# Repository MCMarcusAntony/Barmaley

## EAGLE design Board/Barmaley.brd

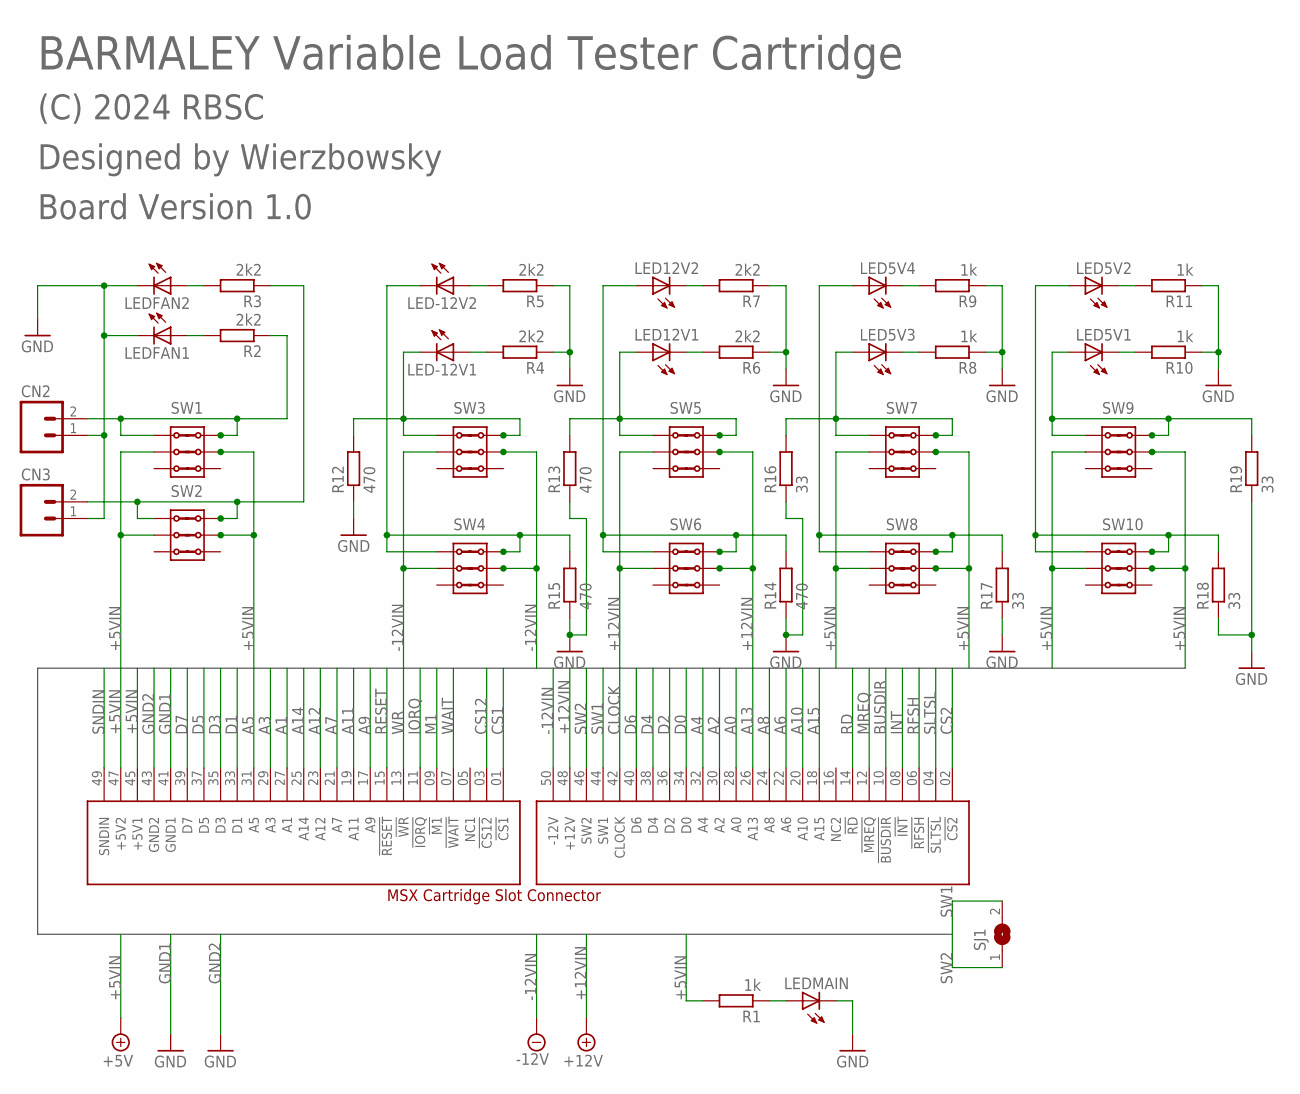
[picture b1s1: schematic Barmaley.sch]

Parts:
CN1: SLOTCONN; MSX_SLOT_CON
CN2, CN3: 2-PIN_FAN_CONNECTOR; MOLEX-X2
LED5V1, LED5V2, LED5V3, LED5V4, LED12V1, LED12V2: LEDSQR2X5; LED2X5
LED-12V1, LED-12V2: LEDSQR2X5; LED2X5
LEDFAN1, LEDFAN2: LEDSQR2X5; LED2X5
LEDMAIN: LED5MM
R1, R8, R9, R10, R11: 1k; R0805
R2, R3, R4, R5, R6, R7: 2k2; R0805
R12, R13, R14, R15: 470; 0617/22
R16, R17, R18, R19: 33; 0617/22
SJ1: SJ
SW1, SW2, SW3, SW4, SW5, SW6, SW7, SW8, SW9, SW10: 2-POSITION_SWITCH; 2PSW

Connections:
+5VIN: CN1.45 (+5V1), CN1.47 (+5V2), R1.2, SW1.2.1, SW1.2.2, SW2.2.1, SW2.2.2, SW7.2.1, SW7.2.2, SW8.2.1, SW8.2.2, SW9.2.1, SW9.2.2, SW10.2.1, SW10.2.2
+12VIN: CN1.48 (+12V), SW5.2.1, SW5.2.2, SW6.2.1, SW6.2.2
-12VIN: CN1.50 (-12V), SW3.2.1, SW3.2.2, SW4.2.1, SW4.2.2
A0: CN1.28 (A0)
A1: CN1.27 (A1)
A2: CN1.30 (A2)
A3: CN1.29 (A3)
A4: CN1.32 (A4)
A5: CN1.31 (A5)
A6: CN1.22 (A6)
A7: CN1.21 (A7)
A8: CN1.24 (A8)
A9: CN1.17 (A9)
A10: CN1.20 (A10)
A11: CN1.19 (A11)
A12: CN1.23 (A12)
A13: CN1.26 (A13)
A14: CN1.25 (A14)
A15: CN1.18 (A15)
BUSDIR: CN1.10 (!BUSDIR)
CLOCK: CN1.42 (CLOCK)
CS1: CN1.01 (!CS1)
CS2: CN1.02 (!CS2)
CS12: CN1.03 (!CS12)
D0: CN1.34 (D0)
D1: CN1.33 (D1)
D2: CN1.36 (D2)
D3: CN1.35 (D3)
D4: CN1.38 (D4)
D5: CN1.37 (D5)
D6: CN1.40 (D6)
D7: CN1.39 (D7)
GND: CN2.1, CN3.1, LEDFAN1.K (C), LEDFAN2.K (C), LEDMAIN.K (C), R4.1, R5.1, R6.1, R7.1, R8.1, R9.1, R10.1, R11.1, R12.1, R13.1, R14.1, R15.1, R16.1, R17.1, R18.1, R19.1
GND1: CN1.41 (GND1)
GND2: CN1.43 (GND2)
GND3: LED-12V1.K (C), R12.2, SW3.3.1, SW3.3.2
GND4: LED-12V2.K (C), R15.2, SW4.3.1, SW4.3.2
INT: CN1.08 (!INT)
IORQ: CN1.11 (!IORQ)
M1: CN1.09 (!M1)
MREQ: CN1.12 (!MREQ)
unnamed: LEDMAIN.A, R1.1
unnamed: CN2.2, R2.1, SW1.3.1, SW1.3.2
unnamed: CN3.2, R3.1, SW2.3.1, SW2.3.2
unnamed: LEDFAN1.A, R2.2
unnamed: LEDFAN2.A, R3.2
unnamed: LED-12V1.A, R4.2
unnamed: LED-12V2.A, R5.2
unnamed: LED12V1.K (C), R6.2
unnamed: LED12V2.K (C), R7.2
unnamed: LED5V4.K (C), R9.2
unnamed: LED5V3.K (C), R8.2
unnamed: LED5V1.K (C), R10.2
unnamed: LED5V2.K (C), R11.2
unnamed: LED12V1.A, R13.2, SW5.3.1, SW5.3.2
unnamed: LED12V2.A, R14.2, SW6.3.1, SW6.3.2
unnamed: LED5V4.A, R17.2, SW8.3.1, SW8.3.2
unnamed: LED5V3.A, R16.2, SW7.3.1, SW7.3.2
unnamed: LED5V1.A, R19.2, SW9.3.1, SW9.3.2
unnamed: LED5V2.A, R18.2, SW10.3.1, SW10.3.2
RD: CN1.14 (!RD)
RESET: CN1.15 (!RESET)
RFSH: CN1.06 (!RFSH)
SLTSL: CN1.04 (!SLTSL)
SNDIN: CN1.49 (SNDIN)
SW1: CN1.44 (SW1), SJ1.2
SW2: CN1.46 (SW2), SJ1.1
WAIT: CN1.07 (!WAIT)
WR: CN1.13 (!WR)

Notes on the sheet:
BARMALEY Variable Load Tester Cartridge
(C) 2024 RBSC
Designed by Wierzbowsky
Board Version 1.0

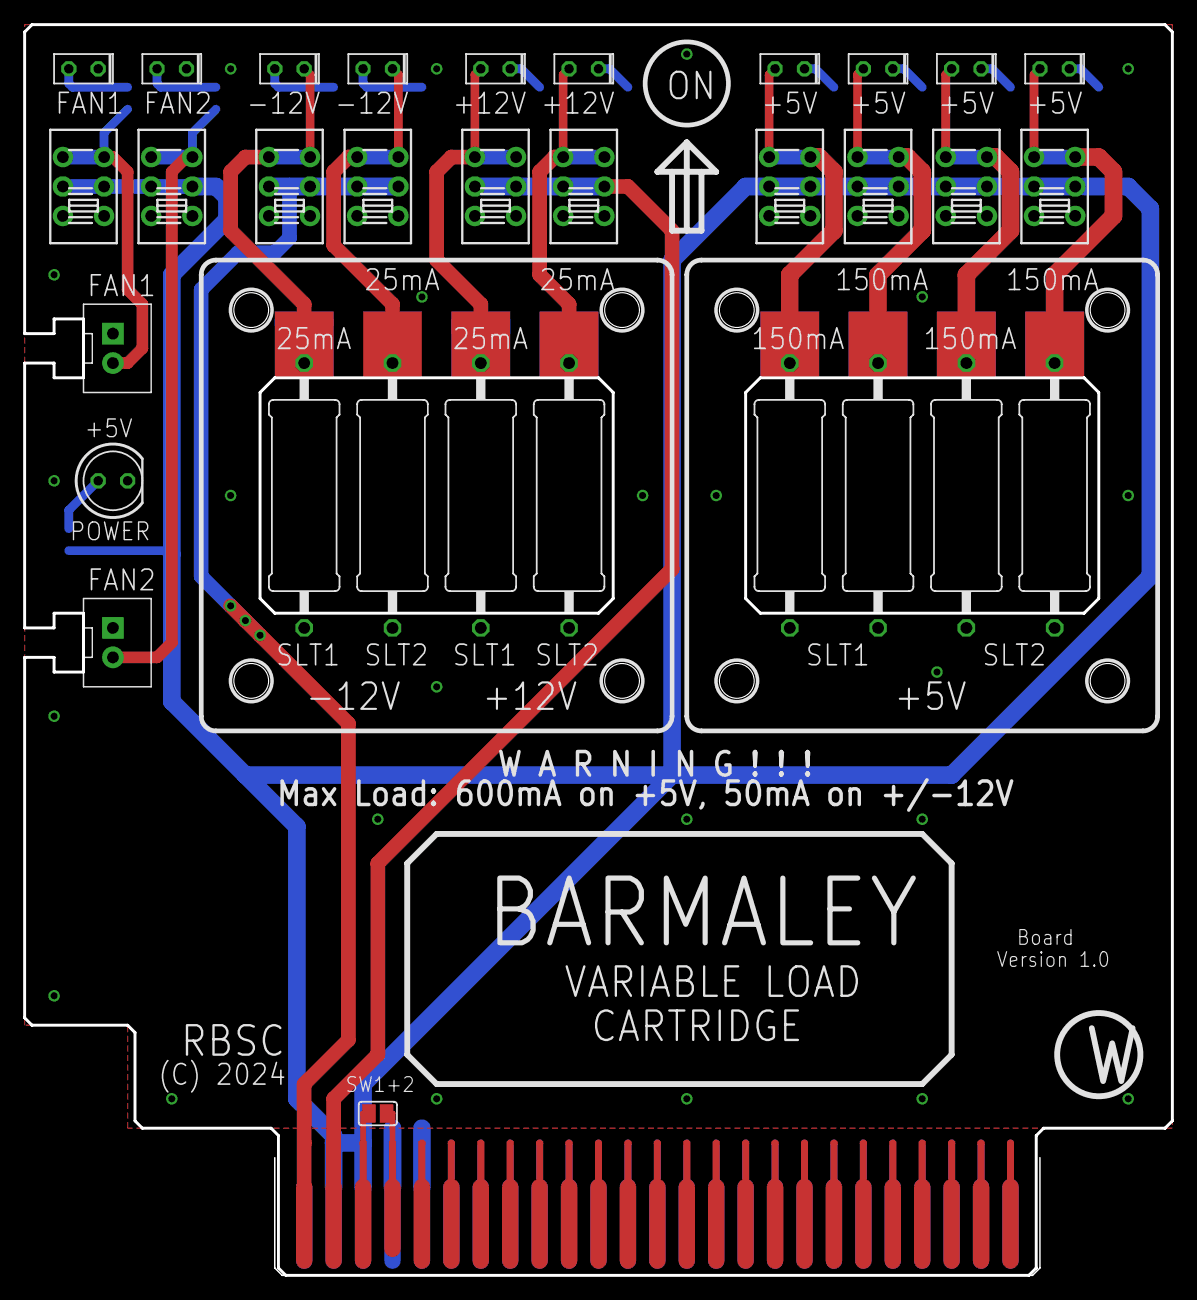
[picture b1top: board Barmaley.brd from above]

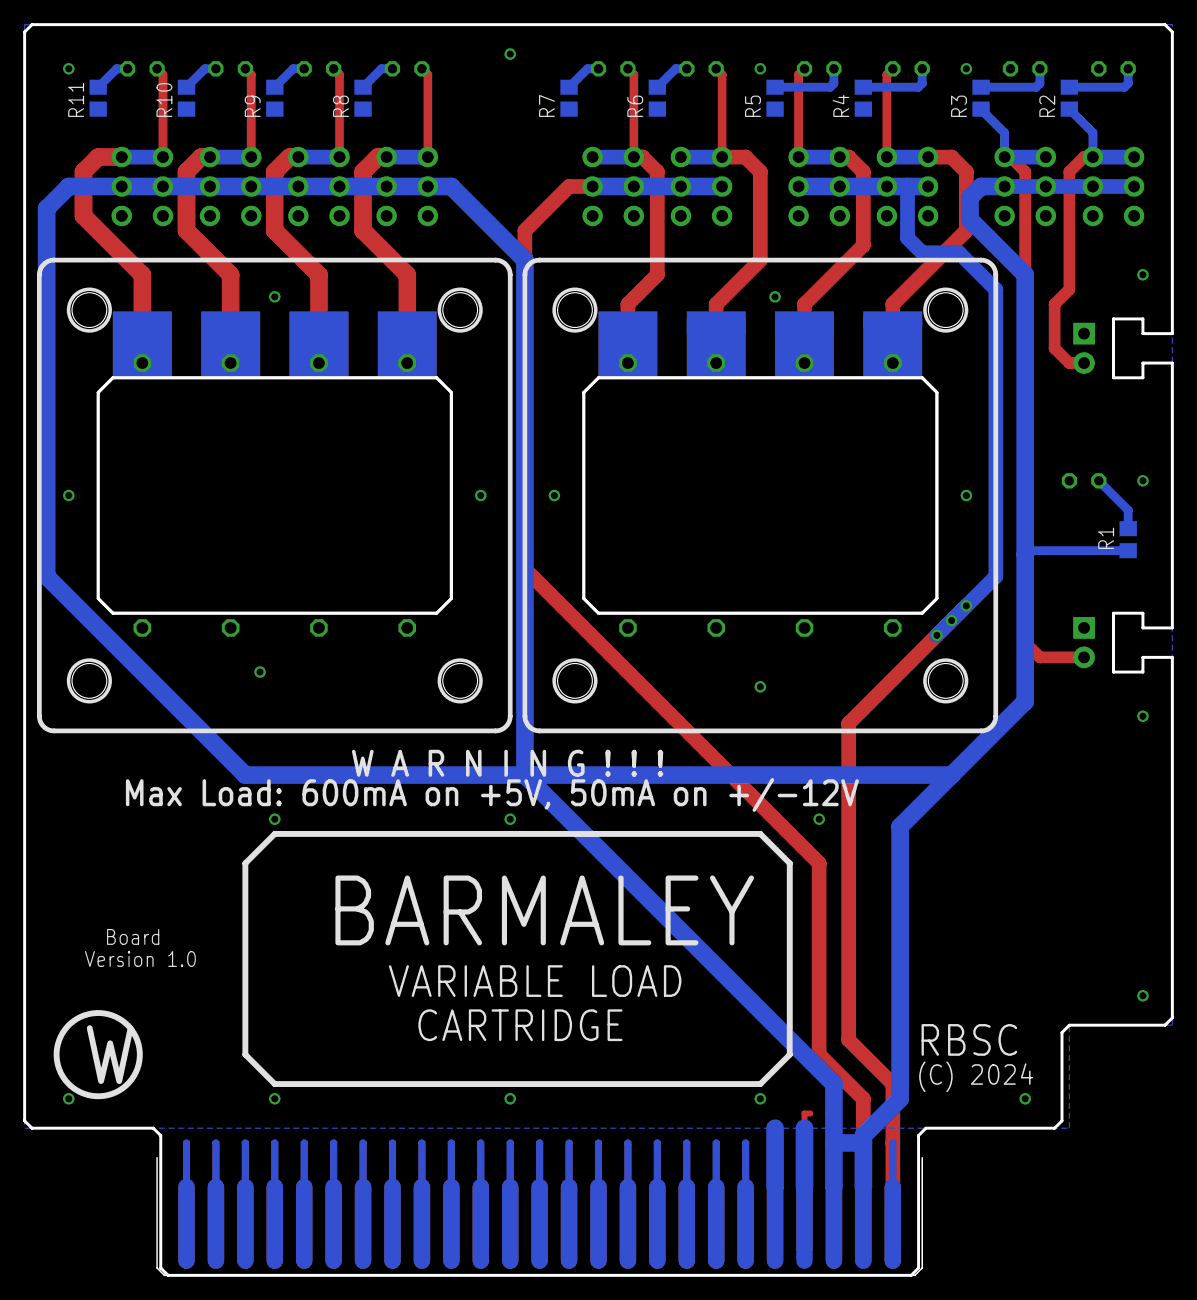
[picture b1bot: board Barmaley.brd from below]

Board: 2 copper layers, 99.1 x 108.0 mm, 44 parts (11 on the bottom side), 27 nets.

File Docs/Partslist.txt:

Partlist

Assembly variant: 

Part     Value               Device              Package      Library       Sheet

CN2      2-PIN_FAN_CONNECTOR 2-PIN_FAN_CONNECTOR MOLEX-X2     fan_conn      1
CN3      2-PIN_FAN_CONNECTOR 2-PIN_FAN_CONNECTOR MOLEX-X2     fan_conn      1
LED-12V1                     LEDSQR2X5           LED2X5       led           1
LED-12V2                     LEDSQR2X5           LED2X5       led           1
LED5V1                       LEDSQR2X5           LED2X5       led           1
LED5V2                       LEDSQR2X5           LED2X5       led           1
LED5V3                       LEDSQR2X5           LED2X5       led           1
LED5V4                       LEDSQR2X5           LED2X5       led           1
LED12V1                      LEDSQR2X5           LED2X5       led           1
LED12V2                      LEDSQR2X5           LED2X5       led           1
LEDFAN1                      LEDSQR2X5           LED2X5       led           1
LEDFAN2                      LEDSQR2X5           LED2X5       led           1
LEDMAIN                      LED5MM              LED5MM       led           1
R1       1k                  R-EU_R0805          R0805        resistor      1
R2       2k2                 R-EU_R0805          R0805        resistor      1
R3       2k2                 R-EU_R0805          R0805        resistor      1
R4       2k2                 R-EU_R0805          R0805        resistor      1
R5       2k2                 R-EU_R0805          R0805        resistor      1
R6       2k2                 R-EU_R0805          R0805        resistor      1
R7       2k2                 R-EU_R0805          R0805        resistor      1
R8       1k                  R-EU_R0805          R0805        resistor      1
R9       1k                  R-EU_R0805          R0805        resistor      1
R10      1k                  R-EU_R0805          R0805        resistor      1
R11      1k                  R-EU_R0805          R0805        resistor      1
R12      470                 R-EU_0617/22        0617/22      resistor      1
R13      470                 R-EU_0617/22        0617/22      resistor      1
R14      470                 R-EU_0617/22        0617/22      resistor      1
R15      470                 R-EU_0617/22        0617/22      resistor      1
R16      33                  R-EU_0617/22        0617/22      resistor      1
R17      33                  R-EU_0617/22        0617/22      resistor      1
R18      33                  R-EU_0617/22        0617/22      resistor      1
R19      33                  R-EU_0617/22        0617/22      resistor      1
SW1      2-POSITION_SWITCH   2-POSITION_SWITCH   2PSW         2pos_switch   1
SW2      2-POSITION_SWITCH   2-POSITION_SWITCH   2PSW         2pos_switch   1
SW3      2-POSITION_SWITCH   2-POSITION_SWITCH   2PSW         2pos_switch   1
SW4      2-POSITION_SWITCH   2-POSITION_SWITCH   2PSW         2pos_switch   1
SW5      2-POSITION_SWITCH   2-POSITION_SWITCH   2PSW         2pos_switch   1
SW6      2-POSITION_SWITCH   2-POSITION_SWITCH   2PSW         2pos_switch   1
SW7      2-POSITION_SWITCH   2-POSITION_SWITCH   2PSW         2pos_switch   1
SW8      2-POSITION_SWITCH   2-POSITION_SWITCH   2PSW         2pos_switch   1
SW9      2-POSITION_SWITCH   2-POSITION_SWITCH   2PSW         2pos_switch   1
SW10     2-POSITION_SWITCH   2-POSITION_SWITCH   2PSW         2pos_switch   1

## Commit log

2025-07-06 Initial release 06.07.2025
    Initial release of Barmaley project's files
2025-07-13 Updated 13.07.2025
    Disclaimer was added
2025-07-26 Revert "Create Gerber.zip"
    This reverts commit dfbb827696817c8db73d86021c8c17b841bd8bdf.
